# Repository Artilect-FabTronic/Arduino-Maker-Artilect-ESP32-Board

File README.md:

# Arduino-Maker-Artilect-ESP32-Board

Conception d'une carte électronique permettant d'accueillir le module **ESP32-WROOM-32D** pour les ateliers Arduino ESP32 :

<!--

-->
<html>
<table align='left' border='0' cellpadding='0'>
<tr class="noBorder">
<td>
<div style="margin: 0 auto; text-align: center">

</div>
</td>
</tr>
<tr class="noBorder">
<td>
<b>*** Objectifs ***</b><br />
Initiation à l'électronique pour débutant, souhaitant acquérir les bonnes pratiques de développement, pour la mise en œuvre des systèmes embarqués à base de cartes Arduino type ESP32 :<br /><br />
<ul>
  <li>Découvrir la programmation des cartes Arduino en langage C/C++ à travers des cas pratiques.</li>
  <li>Précautions de mise en œuvre, sécurité d’utilisation, alimentation de la carte et des périphériques.</li>
  <li>Prise en main des cartes microcontrôleurs ESP32.</li>
  <li>Mise en œuvre de nombreux périphériques d’entrée/sortie.</li>
  <li>Mise en oeuvre ESP32 avec PlatformIO.</li>
  <li>Vers les bases d’Arduino et au-delà...</li>
</ul>
</td>
</tr>
<tr class="noBorder">
<td>
<div style="margin: 0 auto; text-align: center">

</div>
</td>
</tr>
</table>
</p>
<hr>
<br />
</html>

[FabTronic](https://artilect.fr/fabtronic/), la section thématique des makers autour de l’électronique.

<html>
<p>
<table align='left' border='0' cellpadding='0'>
<tr class="noBorder">
<td></td>
<td>Pour plus d'informations, venez nous rendre visite sur notre chaîne Discord à l'adresse : <a href="https://discord.gg/aPnZ5Q7w6Q">https://discord.gg/aPnZ5Q7w6Q</a><br />
Une fois connecté au serveur FabTronic, nous vous invitons à vous présenter dans le salon <b><i>#présentation</i></b>
</td>
</tr>
</table>
</p>
<hr>
<br />
</html>

---

## [Documentation](Docs/README.md)

### Logiciel utilisé pour la conception de la carte électronique

[KiCad EDA - Logiciel open source de capture schématique et de conception de circuits imprimés](https://kicad.org/)

Téléchargement [Windows All Stable Releases > kicad-6.0.10-x86_64.exe](https://downloads.kicad.org/kicad/windows/explore/stable)

[Logiciel open source](https://fr.wikipedia.org/wiki/Open_source) [EDA](https://fr.wikipedia.org/wiki/Conception_assist%C3%A9e_par_ordinateur_pour_l%27%C3%A9lectronique) / [CAO électronique](https://en.wikipedia.org/wiki/Comparison_of_EDA_software) pour Windows, macOS et Linux.

[Retrouvez la schématique de la carte, ainsi que la liste de matériels nécessaire pour l'assemblage (BOM).](Docs/README.md)

---

## Open Source Hardware Association

<!--  -->

<html>
<div style="margin: 0 auto; text-align: left">
<table align='left' border='0' cellpadding='0'>
<tr class="noBorder">
<td align='center' border='0'></td>
<tr class="noBorder">
<td align='center' border='0'><a href="https://www.oshwa.org/" title="" target="_blank">Source : https://www.oshwa.org/</a></td>
</tr>
</table>
</div>
</html>

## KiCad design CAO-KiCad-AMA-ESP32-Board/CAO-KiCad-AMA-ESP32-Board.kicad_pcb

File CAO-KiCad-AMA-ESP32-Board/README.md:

# Réalisation du PCB

## Board Stackup > Design Rules

### Grosses pistes

Net Class = Default
Clearance = 0.34 mm
Track Width = 1 mm
Via Size = 1 mm
Via Hole = 0.4 mm

### https://jlcpcb.com/capabilities/pcb-capabilities

Net Class = Default
Clearance = 0.14 mm
Track Width = 0.14 mm
Via Size = 0.5 mm
Via Hole = 0.3 mm

## INTRODUCTION TO THE ESP32 GUIDE SERIES

[Digital Output Experiment Using An LED](https://techexplorations.com/guides/esp32/begin/digitalout/)

BEGINNER’S GUIDE TO THE 595 SHIFT REGISTER
https://www.idogendel.com/en/archives/211

Cours Systèmes Embarqués: BUS I2C
https://www.technologuepro.com/cours-systemes-embarques/cours-systemes-embarques-Bus-I2C.htm
http://electro8051.free.fr/I2C/busi2c.htm

## JLCPCB

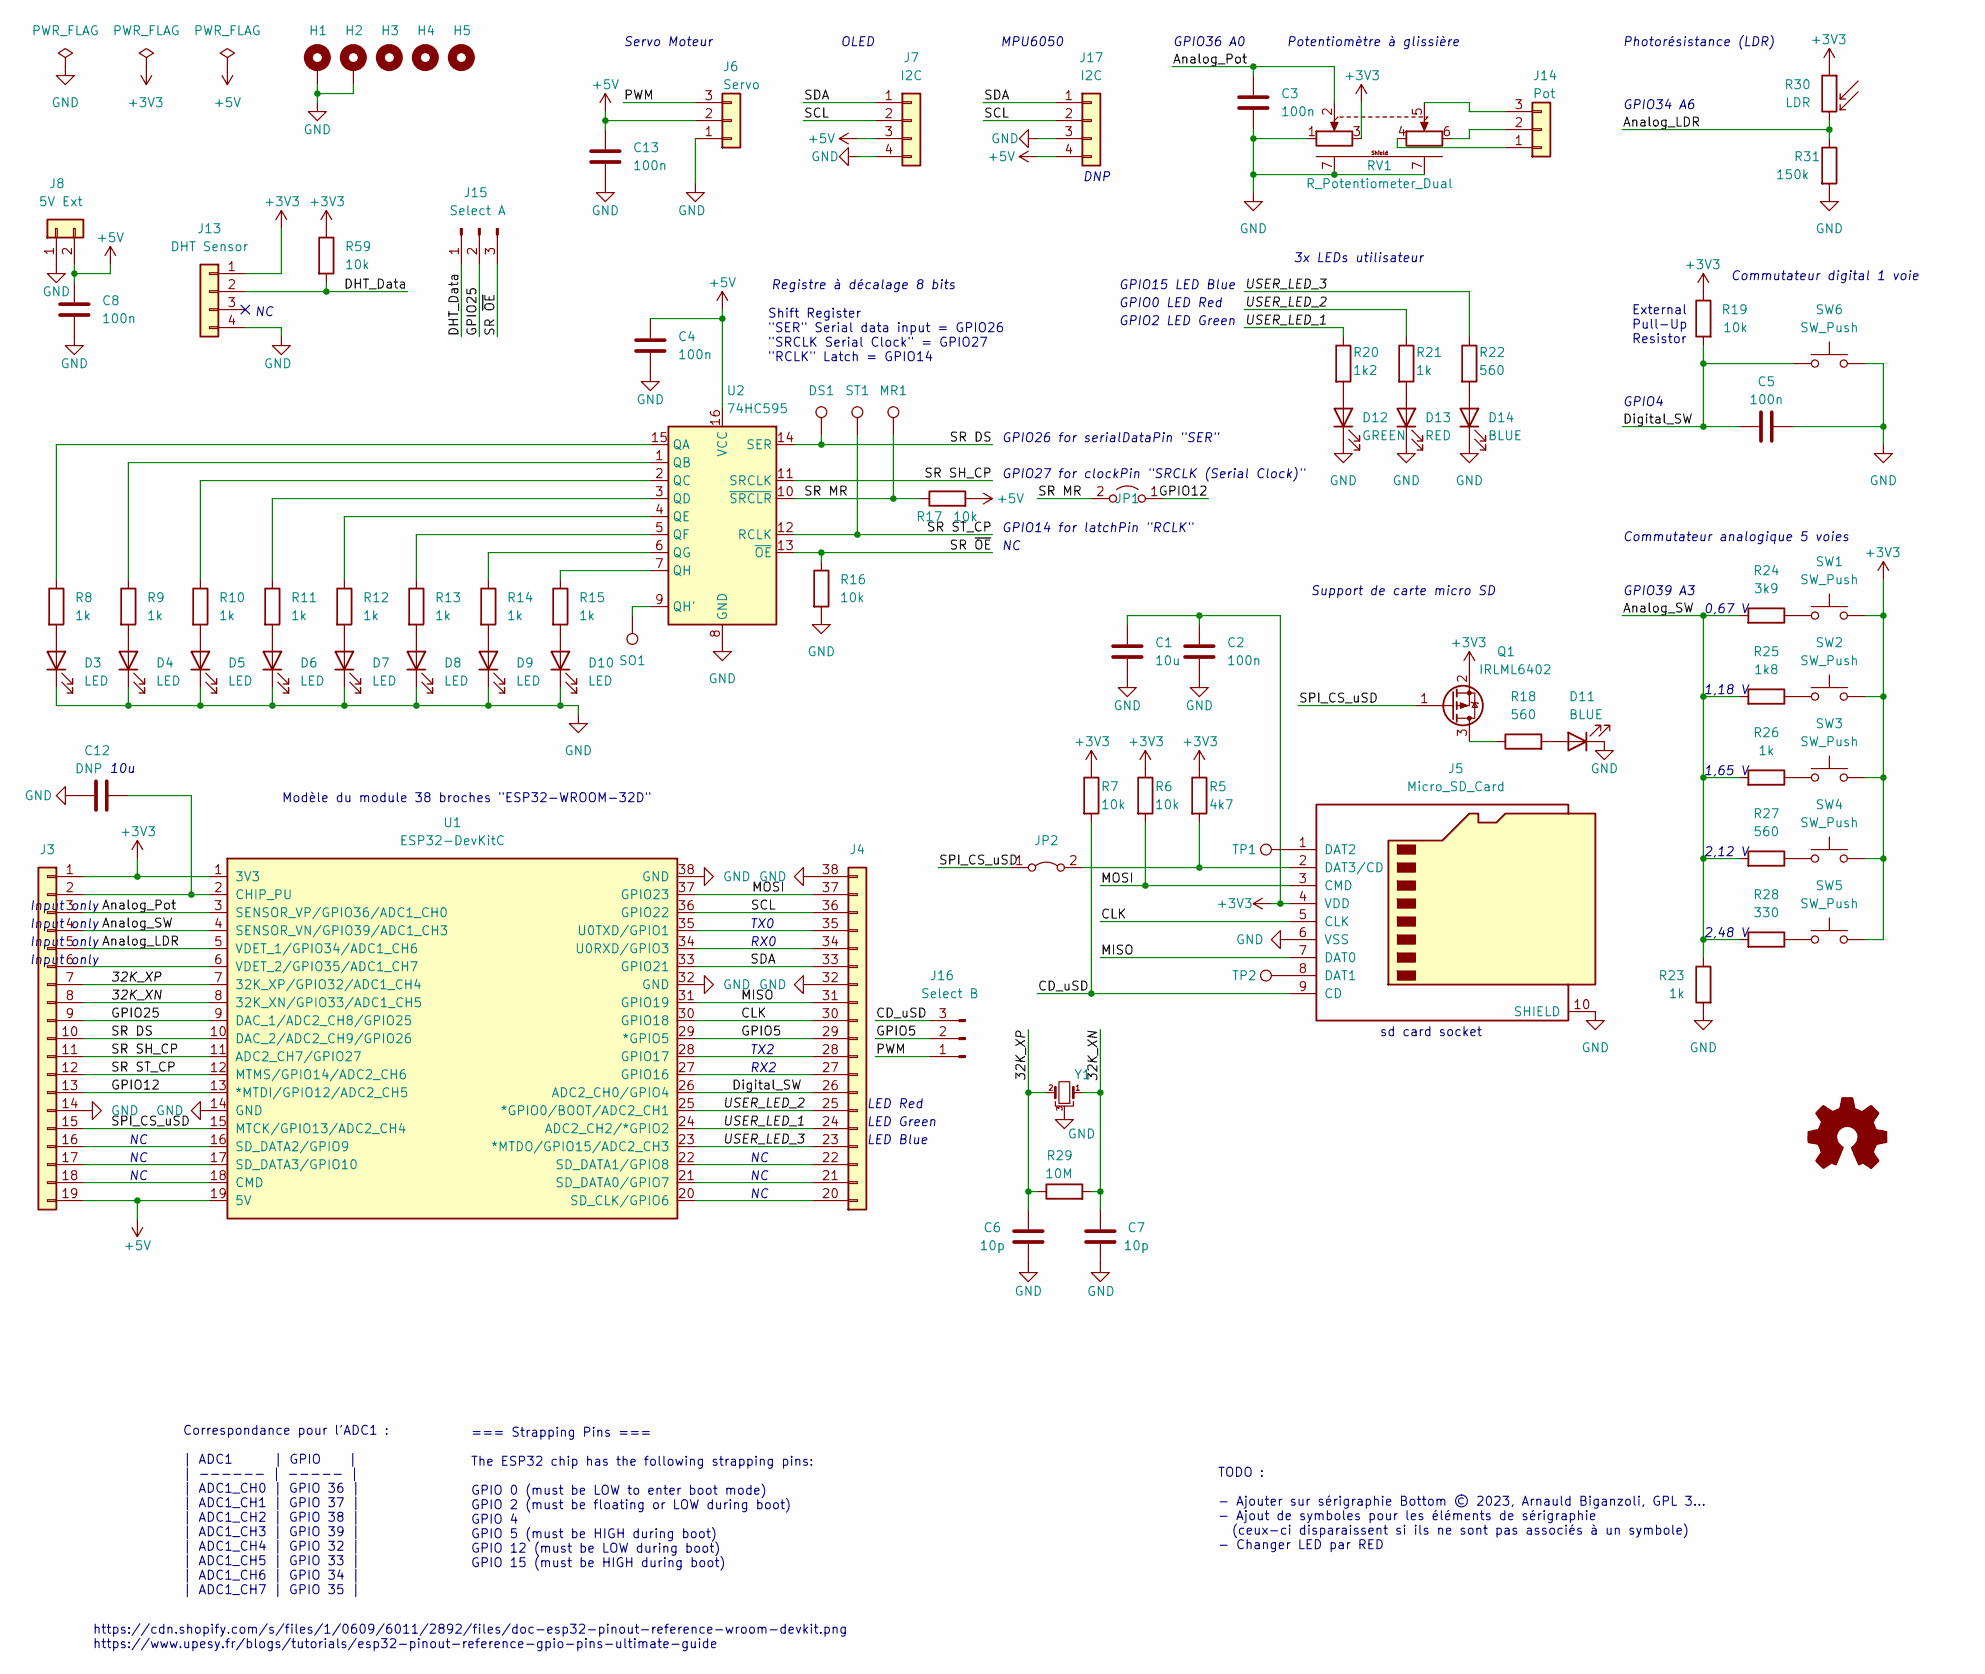
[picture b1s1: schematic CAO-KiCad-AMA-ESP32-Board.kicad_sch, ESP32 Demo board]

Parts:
C1: 10u; C_0805_2012Metric_Pad1.18x1.45mm_HandSolder
C2, C3, C4, C5, C8, C13: 100n; C_0805_2012Metric_Pad1.18x1.45mm_HandSolder
C6, C7: 10p; C_0805_2012Metric_Pad1.18x1.45mm_HandSolder
C12: DNP; C_0805_2012Metric_Pad1.18x1.45mm_HandSolder
D3, D4, D5, D6, D7, D8, D9, D10: LED; LED_0603_1608Metric_Pad1.05x0.95mm_HandSolder
D11: BLUE; LED_0603_1608Metric_Pad1.05x0.95mm_HandSolder
D12: GREEN; LED_0805_2012Metric_Pad1.15x1.40mm_HandSolder
D13: RED; LED_0805_2012Metric_Pad1.15x1.40mm_HandSolder
D14: BLUE; LED_0805_2012Metric_Pad1.15x1.40mm_HandSolder
DS1: TestPoint; TestPoint_Pad_D2.0mm
H1, H2: MountingHole_Pad; MountingHole_3.2mm_M3_ISO7380_Pad_TopBottom
H3, H4, H5: MountingHole; MountingHole_3.2mm_M3_ISO7380
J3, J4: Conn_01x19; PinSocket_1x19_P2.54mm_Vertical
J5: Micro_SD_Card; microSD_Yozaka_Interconnects_R2165
J6: Servo; PinHeader_1x03_P2.54mm_Vertical
J7, J17: I2C; PinSocket_1x04_P2.54mm_Vertical
J8: 5V Ext; PinHeader_1x02_P2.54mm_Horizontal
J13: DHT Sensor; PinSocket_1x04_P2.54mm_Vertical
J14: Pot; PinHeader_1x03_P2.54mm_Vertical
J15: Select A; PinHeader_1x03_P2.54mm_Vertical
J16: Select B; SolderJumper-3_P1.3mm_Bridged12_RoundedPad1.0x1.5mm_NumberL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
JP1: Jumper_2_Open; SolderJumper-2_P1.3mm_Open_RoundedPad1.0x1.5mm
JP2: Jumper_2_Bridged; SolderJumper-2_P1.3mm_Bridged_RoundedPad1.0x1.5mm
LOGO1: Logo_Open_Hardware_Small; KiCad-Logo2_5mm_SilkScreen
MR1: TestPoint; TestPoint_Pad_D2.0mm
Q1: IRLML6402; SOT-23
R5: 4k7; R_0805_2012Metric_Pad1.20x1.40mm_HandSolder
R6, R7, R16, R17, R19, R59: 10k; R_0805_2012Metric_Pad1.20x1.40mm_HandSolder
R8, R9, R10, R11, R12, R13, R14, R15, R21, R23, R26: 1k; R_0805_2012Metric_Pad1.20x1.40mm_HandSolder
R18, R22, R27: 560; R_0805_2012Metric_Pad1.20x1.40mm_HandSolder
R20: 1k2; R_0805_2012Metric_Pad1.20x1.40mm_HandSolder
R24: 3k9; R_0805_2012Metric_Pad1.20x1.40mm_HandSolder
R25: 1k8; R_0805_2012Metric_Pad1.20x1.40mm_HandSolder
R28: 330; R_0805_2012Metric_Pad1.20x1.40mm_HandSolder
R29: 10M; R_0805_2012Metric_Pad1.20x1.40mm_HandSolder
R30: LDR; R_LDR_5.1x4.3mm_P3.4mm_Vertical
R31: 150k; R_0805_2012Metric_Pad1.20x1.40mm_HandSolder
RV1: R_Potentiometer_Dual; Potentiometer_B103_Double_Slide
SO1: TestPoint; TestPoint_Pad_D2.0mm
ST1: TestPoint; TestPoint_Pad_D2.0mm
SW1, SW2, SW3, SW4, SW5, SW6: SW_Push; SW_PUSH-12mm
TP1, TP2: TestPoint; TestPoint_Pad_D2.0mm
U1: ESP32-DevKitC
U2: 74HC595; SOIC-16_3.9x9.9mm_P1.27mm
Y1: Crystal_GND3_Small; Crystal_AT310_D3.0mm_L10.0mm_Horizontal_1EP_style2

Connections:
+3V3: C1.1, C2.1, J3.1, J5.4 (VDD), J13.1, Q1.2 (S), R5.1, R6.1, R7.1, R19.1, R30.1, R59.1, RV1.3, SW1.2, SW2.2, SW3.2, SW4.2, SW5.2, U1.1 (3V3)
+5V: C4.1, C8.1, C13.1, J3.19, J6.2, J7.3, J8.2, J17.4, R17.2, U1.19 (5V), U2.16 (VCC)
/32K_XN: C7.2, J3.8, R29.2, U1.8 (32K_XN/GPIO33/ADC1_CH5), Y1.1
/32K_XP: C6.2, J3.7, R29.1, U1.7 (32K_XP/GPIO32/ADC1_CH4), Y1.2
/Analog_LDR: J3.5, R30.2, R31.1, U1.5 (VDET_1/GPIO34/ADC1_CH6)
/Analog_Pot: C3.1, J3.3, RV1.2, U1.3 (SENSOR_VP/GPIO36/ADC1_CH0)
/Analog_SW: J3.4, R23.1, R24.2, R25.2, R26.2, R27.2, R28.2, U1.4 (SENSOR_VN/GPIO39/ADC1_CH3)
/CD_uSD: J5.9 (CD), J16.3, R7.2
/CLK: J4.30, J5.5 (CLK), U1.30 (GPIO18)
/DHT_Data: J13.2, J15.1, R59.2
/Digital_SW: C5.2, J4.26, R19.2, SW6.1, U1.26 (ADC2_CH0/GPIO4)
/GPIO5: J4.29, J16.2, U1.29 (*GPIO5)
/GPIO12: J3.13, JP1.1 (A), U1.13 (*MTDI/GPIO12/ADC2_CH5)
/GPIO25: J3.9, J15.2, U1.9 (DAC_1/ADC2_CH8/GPIO25)
/MISO: J4.31, J5.7 (DAT0), U1.31 (GPIO19)
/MOSI: J4.37, J5.3 (CMD), R6.2, U1.37 (GPIO23)
/PWM: J6.3, J16.1
/SCL: J4.36, J7.2, J17.2, U1.36 (GPIO22)
/SDA: J4.33, J7.1, J17.1, U1.33 (GPIO21)
/SPI_CS_uSD: J3.15, JP2.1 (A), Q1.1 (G), U1.15 (MTCK/GPIO13/ADC2_CH4)
/SR DS: DS1.1, J3.10, U1.10 (DAC_2/ADC2_CH9/GPIO26), U2.14 (SER)
/SR MR: JP1.2 (B), MR1.1, R17.1, U2.10 (~SRCLR)
/SR SH_CP: J3.11, U1.11 (ADC2_CH7/GPIO27), U2.11 (SRCLK)
/SR ST_CP: J3.12, ST1.1, U1.12 (MTMS/GPIO14/ADC2_CH6), U2.12 (RCLK)
/SR ~OE: J15.3, R16.1, U2.13 (~OE)
/USER_LED_1: J4.24, R20.1, U1.24 (ADC2_CH2/*GPIO2)
/USER_LED_2: J4.25, R21.1, U1.25 (*GPIO0/BOOT/ADC2_CH1)
/USER_LED_3: J4.23, R22.1, U1.23 (*MTDO/GPIO15/ADC2_CH3)
GND: C1.2, C2.2, C3.2, C4.2, C5.1, C6.1, C7.1, C8.2, C12.2, C13.2, D3.1 (K), D4.1 (K), D5.1 (K), D6.1 (K), D7.1 (K), D8.1 (K), D9.1 (K), D10.1 (K), D11.1 (K), D12.1 (K), D13.1 (K), D14.1 (K), H1.1, H2.1, J3.14, J4.32, J4.38, J5.6 (VSS), J5.10 (SHIELD), J6.1, J7.4, J8.1, J13.4, J17.3, R16.2, R23.2, R31.2, RV1.1, RV1.7 (Shield), SW6.2, U1.14 (GND), U1.32 (GND), U1.38 (GND), U2.8 (GND), Y1.3
unnamed: C12.1, J3.2, U1.2 (CHIP_PU)
unnamed: D3.2 (A), R8.2
unnamed: D4.2 (A), R9.2
unnamed: D5.2 (A), R10.2
unnamed: D6.2 (A), R11.2
unnamed: D7.2 (A), R12.2
unnamed: D8.2 (A), R13.2
unnamed: D9.2 (A), R14.2
unnamed: D10.2 (A), R15.2
unnamed: D11.2 (A), R18.2
unnamed: D12.2 (A), R20.2
unnamed: D13.2 (A), R21.2
unnamed: D14.2 (A), R22.2
unnamed: J3.6, U1.6 (VDET_2/GPIO35/ADC1_CH7)
unnamed: J3.16, U1.16 (SD_DATA2/GPIO9)
unnamed: J3.17, U1.17 (SD_DATA3/GPIO10)
unnamed: J3.18, U1.18 (CMD)
unnamed: J4.20, U1.20 (SD_CLK/GPIO6)
unnamed: J4.21, U1.21 (SD_DATA0/GPIO7)
unnamed: J4.22, U1.22 (SD_DATA1/GPIO8)
unnamed: J4.27, U1.27 (GPIO16)
unnamed: J4.28, U1.28 (GPIO17)
unnamed: J4.34, U1.34 (U0RXD/GPIO3)
unnamed: J4.35, U1.35 (U0TXD/GPIO1)
unnamed: J5.1 (DAT2), TP1.1
unnamed: J5.2 (DAT3/CD), JP2.2 (B), R5.2
unnamed: J5.8 (DAT1), TP2.1
unnamed: J14.1, RV1.4
unnamed: J14.2, RV1.6
unnamed: J14.3, RV1.5
unnamed: Q1.3 (D), R18.1
unnamed: R8.1, U2.15 (QA)
unnamed: R9.1, U2.1 (QB)
unnamed: R10.1, U2.2 (QC)
unnamed: R11.1, U2.3 (QD)
unnamed: R12.1, U2.4 (QE)
unnamed: R13.1, U2.5 (QF)
unnamed: R14.1, U2.6 (QG)
unnamed: R15.1, U2.7 (QH)
unnamed: R24.1, SW1.1
unnamed: R25.1, SW2.1
unnamed: R26.1, SW3.1
unnamed: R27.1, SW4.1
unnamed: R28.1, SW5.1
unnamed: SO1.1, U2.9 (QH')

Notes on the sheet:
Shift Register "SER" Serial data input = GPIO26 "SRCLK Serial Clock" = GPIO27 "RCLK" Latch = GPIO14
Input only
Support de carte micro SD
OLED
GPIO0 LED Red
0,67 V
GPIO39 A3
RX0
LED Green
=== Strapping Pins === The ESP32 chip has the following strapping pins: GPIO 0 (must be LOW to enter boot mode) GPIO 2 (must be floating or LOW during boot) GPIO 4 GPIO 5 (must be HIGH during boot) GPIO 12 (must be LOW during boot) GPIO 15 (must be HIGH during boot)
TX0
https://cdn.shopify.com/s/files/1/0609/6011/2892/files/doc-esp32-pinout-reference-wroom-devkit.png https://www.upesy.fr/blogs/tutorials/esp32-pinout-reference-gpio-pins-ultimate-guide
Servo Moteur
External Pull-Up Resistor
Modèle du module 38 broches "ESP32-WROOM-32D"
3x LEDs utilisateur
Correspondance pour l'ADC1 : | ADC1 | GPIO | | ------ | ----- | | ADC1_CH0 | GPIO 36 | | ADC1_CH1 | GPIO 37 | | ADC1_CH2 | GPIO 38 | | ADC1_CH3 | GPIO 39 | | ADC1_CH4 | GPIO 32 | | ADC1_CH5 | GPIO 33 | | ADC1_CH6 | GPIO 34 | | ADC1_CH7 | GPIO 35 |
1,18 V
LED Blue
TX2
GPIO14 for latchPin "RCLK"
LED Red
RX2
10u
2,48 V
GPIO4
GPIO15 LED Blue
TODO : - Ajouter sur sérigraphie Bottom © 2023, Arnauld Biganzoli, GPL 3... - Ajout de symboles pour les éléments de sérigraphie (ceux-ci disparaissent si ils ne sont pas associés à un symbole) - Changer LED par RED
Commutateur digital 1 voie
GPIO26 for serialDataPin "SER"
GPIO2 LED Green
sd card socket
GPIO27 for clockPin "SRCLK (Serial Clock)"
Commutateur analogique 5 voies
MPU6050
GPIO34 A6
DNP
Registre à décalage 8 bits
Photorésistance (LDR)
GPIO36 A0

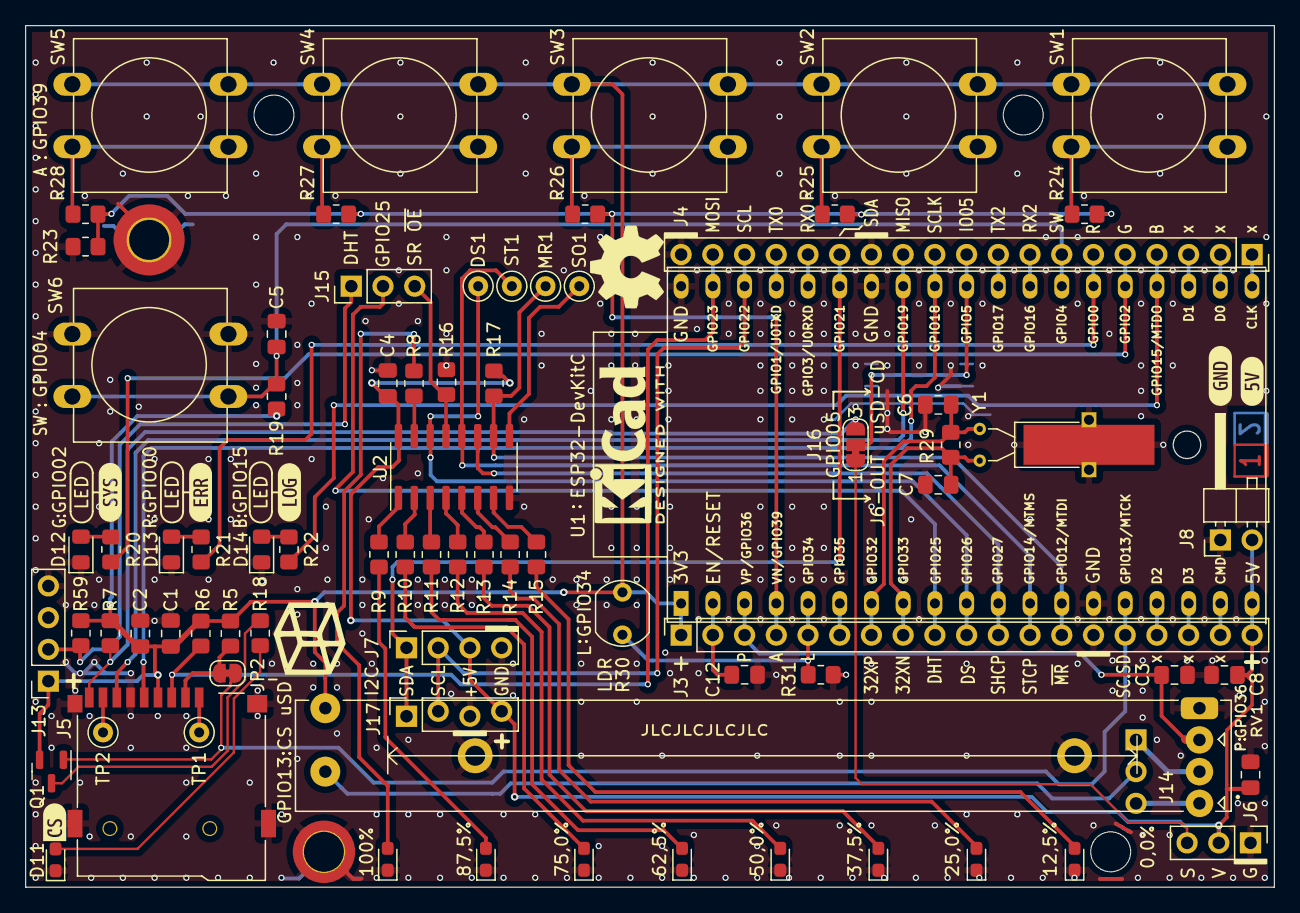
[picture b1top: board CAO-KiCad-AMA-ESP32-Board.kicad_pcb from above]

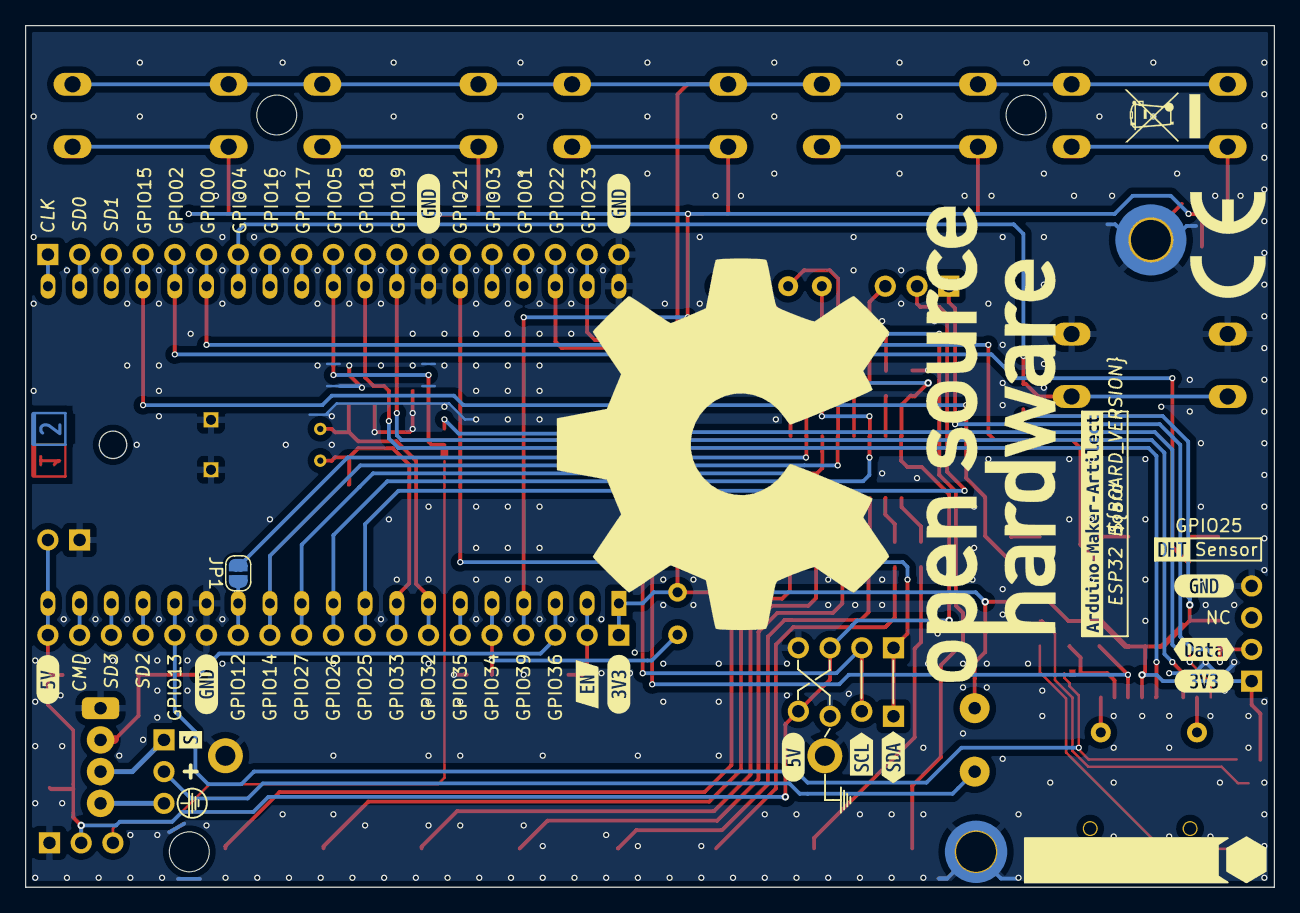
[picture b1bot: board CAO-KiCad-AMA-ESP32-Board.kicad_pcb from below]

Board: 2 copper layers, 100.0 x 69.0 mm, 108 parts (16 on the bottom side), 74 nets.

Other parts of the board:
Layer-x2: VAL**; Layer-indicator-two-side
kibuzzard-1, kibuzzard-1#2, kibuzzard-1#3: G***; kibuzzard-6367F8E9
kibuzzard-63A1FAC6: G***; kibuzzard-63A1FAC6
kibuzzard-63A1FB19: G***; kibuzzard-63A1FB19
kibuzzard-63A33E4B, kibuzzard-63A33E4B#2: G***; kibuzzard-63A33E4B
kibuzzard-63A33F4C: G***; kibuzzard-63A33F4C
kibuzzard-63A45C8C: G***; kibuzzard-63A45C8C
kibuzzard-63A457E7: G***; kibuzzard-63A457E7
kibuzzard-63A470E3: G***; kibuzzard-63A470E3
kibuzzard-63A34430: G***; kibuzzard-63A34430
kibuzzard-63A45813: G***; kibuzzard-63A45813
kibuzzard-63A48047: G***; kibuzzard-63A48047
kibuzzard-63ADDA63: G***; kibuzzard-63ADDA63
kibuzzard-639F4895: G***; kibuzzard-639F4895
kibuzzard-6367FF54, kibuzzard-6367FF54#2, kibuzzard-6367FF54#3, kibuzzard-6367FF54#4, kibuzzard-6367FF54#5: G***; kibuzzard-6367FF54

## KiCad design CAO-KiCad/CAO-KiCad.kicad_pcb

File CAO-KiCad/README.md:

# Carte électronique d'accueil du module ESP32-WROOM-32D

Le module ESP32-DEVKITC-32D possède 38 broches et les dimensions sont :

Voir les détails de la [Datasheet](https://dl.espressif.com/dl/schematics/esp32_devkitc_v4-sch.pdf) du module.

PMF370XN, Not recommended for new designs (NRND), Alternatives PMF250XNE
N-channel TrenchMOS extremely low level FET
https://www.nexperia.com/products/mosfets/small-signal-mosfets/PMF370XN.html
https://assets.nexperia.com/documents/data-sheet/PMF370XN.pdf
https://fr.farnell.com/nexperia/pmf370xn-115/transistor-mosfet-n-30v-870ma/dp/1758096
Type de boîtier de transistor: SOT-323
Modèle composant équivalent sous KiCad : BS170F, BS870, 2N7002E, H, K, AO3400A***

Transistor de puissance Mosfet 20V 3.7A, 100 pièces, IRLML6402 sot-23 p-channel
https://fr.aliexpress.com/item/32716087801.html
https://www.infineon.com/cms/en/product/power/mosfet/p-channel/irlml6402/
https://www.infineon.com/dgdl/Infineon-IRLML6402-DataSheet-v01_01-EN.pdf?fileId=5546d462533600a401535668d5c2263c

TODO CAD Models: Symbol, Footprint, 3D Model

[Faire une demande de quotation du PCB chez NextPCB](https://www.nextpcb.com/pcb-quote?layer=4&length=&width=&count=10&height=1.6).

PCB Calculator

* PCB file: Gerber-Files
* Material: Fr-4
* Layer Count: 4 Layers
* TG: TG130
* Board Type: Single piece
* Size(single): l x L mm
* Quantity (single): 10
* PCB Thickness: 1.6
* Solder Mask Color: Green
* Silkscreen: White
* Finished Copper Weight: 1oz
* Inner Copper Weight: 0.5oz
* Min. Trace / Space Outer: 6/6mil
* Min. Drilled Hole: 0.3mm
* Via Process: Tenting Vias
* Surface Finish: HASL
* Beveling of G/F: NO
* Electrical Test: Sample Test Free
* Approve Working Gerber: Don't need
* Plated Half-holes/Castellated Holes: NO
* Impedance: NO
* Microsection Analysis Report: NO

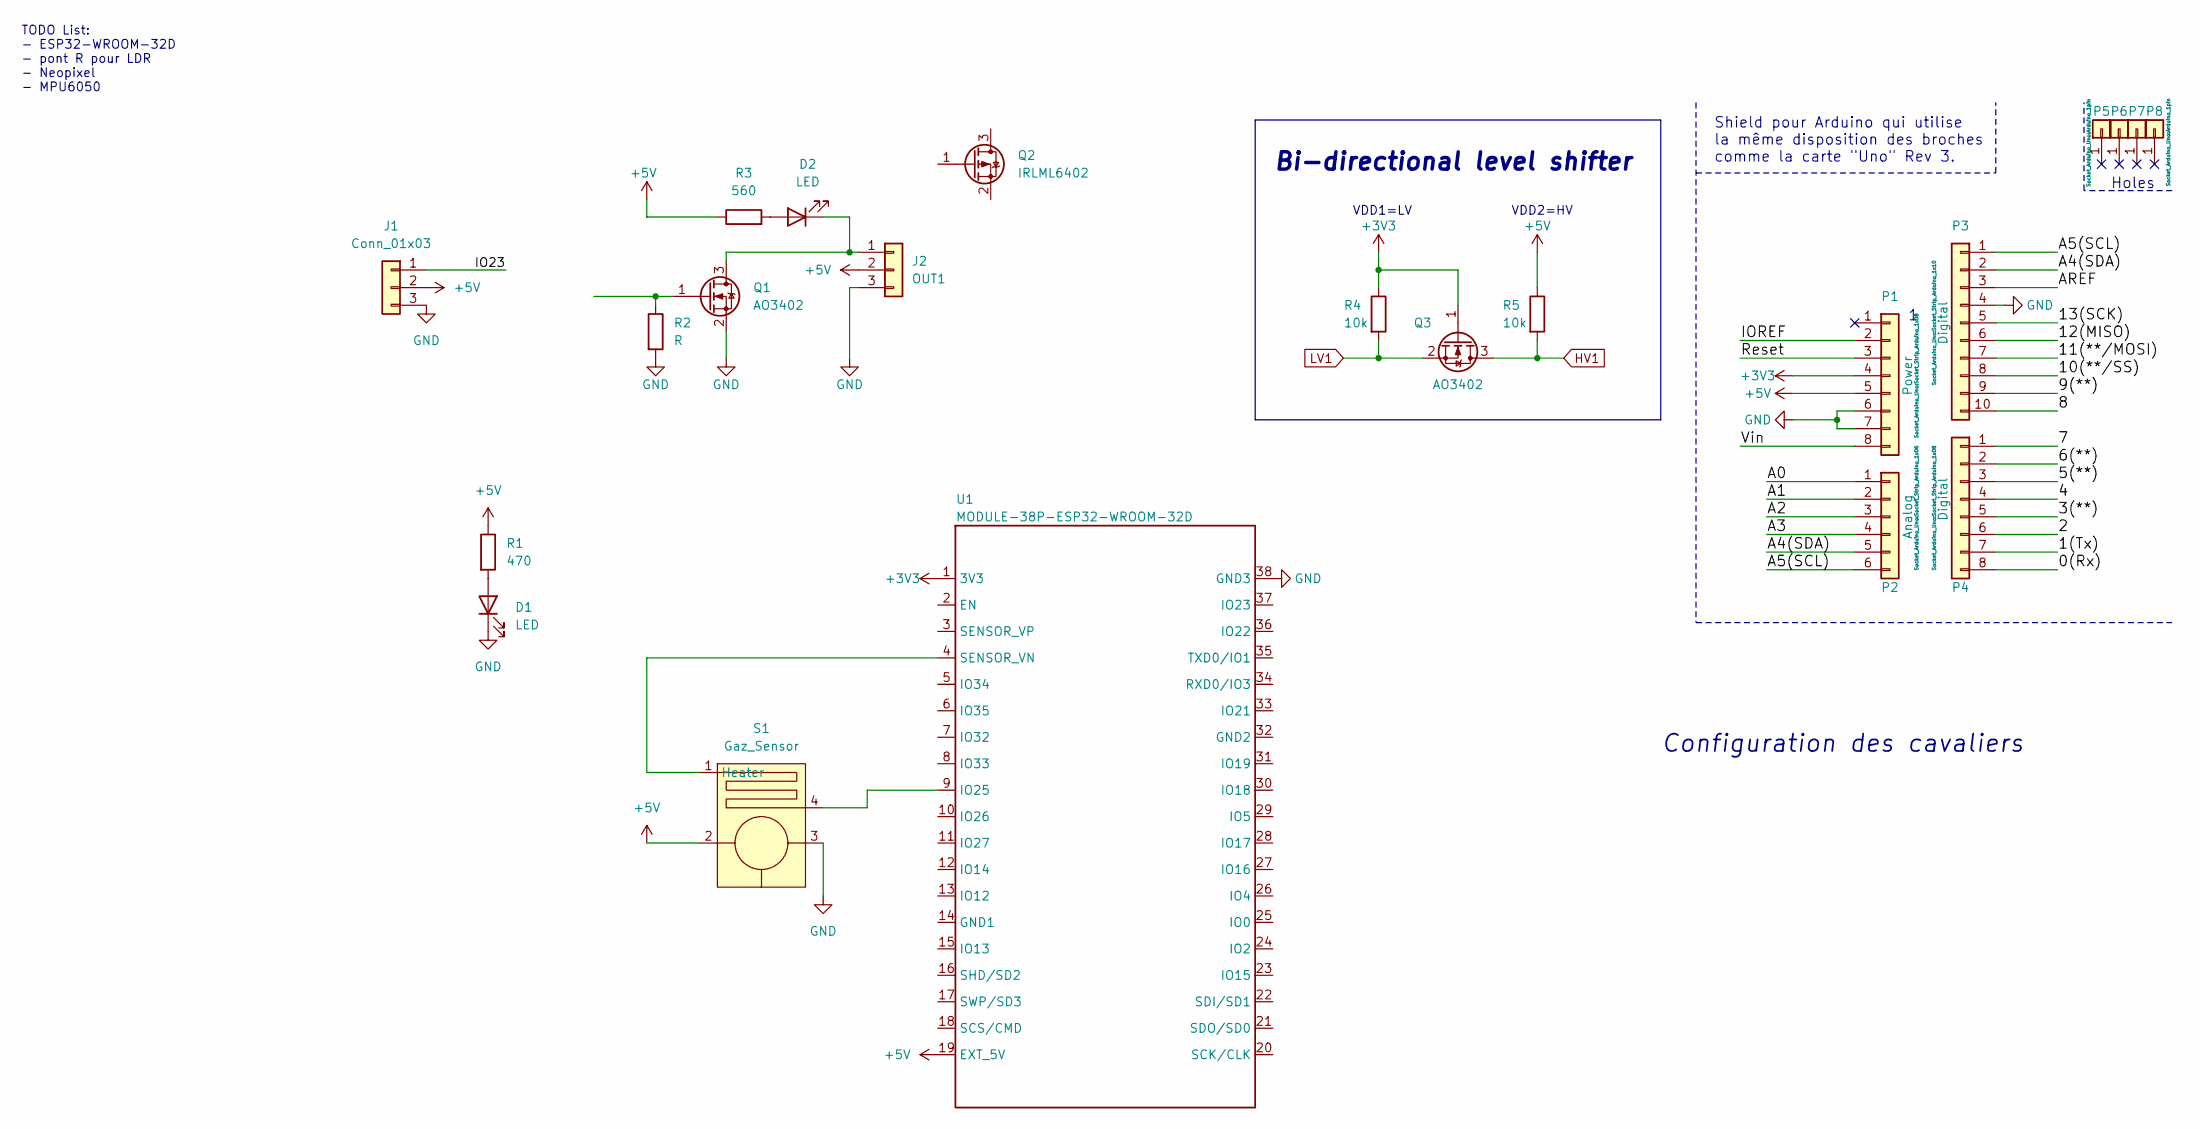
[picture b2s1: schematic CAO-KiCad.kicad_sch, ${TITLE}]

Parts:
D1, D2: LED; LED_0805_2012Metric_Pad1.15x1.40mm_HandSolder
J1: Conn_01x03; PinHeader_1x03_P2.54mm_Vertical
J2: OUT1; PinHeader_1x03_P2.54mm_Vertical
P1: Power; Socket_Strip_Arduino_1x08
P2: Analog; Socket_Strip_Arduino_1x06
P3: Digital; Socket_Strip_Arduino_1x10
P4: Digital; Socket_Strip_Arduino_1x08
P5, P6, P7, P8: CONN_01X01; Arduino_1pin
Q1, Q3: AO3402; SOT-23
Q2: IRLML6402; SOT-23
R1: 470; R_0805_2012Metric_Pad1.20x1.40mm_HandSolder
R2: R; R_0805_2012Metric_Pad1.20x1.40mm_HandSolder
R3: 560; R_0805_2012Metric_Pad1.20x1.40mm_HandSolder
R4, R5: 10k; R_0805_2012Metric_Pad1.20x1.40mm_HandSolder
S1: Gaz_Sensor; TO-5-2_Window
U1: MODULE-38P-ESP32-WROOM-32D; ESP32-WROOM-32

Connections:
+3V3: P1.4, Q3.1 (G), R4.1, U1.1 (3V3)
+5V: J1.2, J2.2, P1.5, R1.1, R3.1, R5.1, S1.2, U1.19 (EXT_5V)
/0(Rx): P4.8
/1(Tx): P4.7
/2: P4.6
/3(**): P4.5
/4: P4.4
/5(**): P4.3
/6(**): P4.2
/7: P4.1
/8: P3.10
/9(**): P3.9
/10(**/SS): P3.8
/11(**/MOSI): P3.7
/12(MISO): P3.6
/13(SCK): P3.5
/A0: P2.1
/A1: P2.2
/A2: P2.3
/A3: P2.4
/A4(SDA): P2.5, P3.2
/A5(SCL): P2.6, P3.1
/AREF: P3.3
/IO23: J1.1
/IOREF: P1.2
/Reset: P1.3
/Vin: P1.8
GND: D1.1 (K), J1.3, J2.3, P1.6, P1.7, P3.4, Q1.2 (S), R2.2, S1.3, U1.38 (GND3)
HV1: Q3.3 (D), R5.2
LV1: Q3.2 (S), R4.2
unnamed: D1.2 (A), R1.2
unnamed: D2.1 (K), J2.1, Q1.3 (D)
unnamed: D2.2 (A), R3.2
unnamed: Q1.1 (G), R2.1
unnamed: S1.4, U1.9 (IO25)
unnamed: S1.1 (Heater), U1.4 (SENSOR_VN)

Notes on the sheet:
TODO List: - ESP32-WROOM-32D - pont R pour LDR - Neopixel - MPU6050
VDD2=HV
Holes
Shield pour Arduino qui utilise la même disposition des broches comme la carte "Uno" Rev 3.
VDD1=LV
Bi-directional level shifter
Configuration des cavaliers

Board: 4 copper layers, 22 parts (0 on the bottom side), 13 nets, no tracks yet.

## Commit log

2021-11-22 Add link
2021-11-26 Creation du projet KiCad
2021-11-26 Mise a jour de la doc
2021-11-26 maj readme
2021-11-26 ajout d'image
2021-11-29 Debut de la creation du module ESP32
2021-11-29 Arrangement des broches du symbole de l'ESP32
2021-12-01 MAJ empreinte
2022-12-30 Remplacement du forme factor Uno par la carte A-M-A avec ESP32-WROOM-32D 38 broches
2022-12-30 Ajout du schématique et de la BOM
2022-12-31 Mise à jour de la BOM
2023-01-08 Correction majeur sur le GPIO12, doit-être à l'état bas lors du démarrage de l'ESP32
2023-03-01 MAJ valeurs R pour LEDs
